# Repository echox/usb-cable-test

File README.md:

# USB Cable Tester
This is a simple tester for USB cables with USB A and Micro USB B.

## Usage

### Cable test
Connect a cable to both ends of the tester. All four LEDs should light up.

If a LED isn't lighting up the corresponding wire might be broken or not connected.
Some cables come without the wires for data transmitting. These type of cables is only suiteable for slow charging a device and can be easily detected if the LEDs for D+ and D- are not connected.

### Battery test
To check if the battery is working disconnect any connected cable.
Press the button. All LEDs should light up.

### Testpads
You can also use the testpads for checking the data lines of your cable.
Connect a probe of your multimeter to TP1 and then check every other testpad for a connection.

## Build
The build is straightforward but contains SMD components with a small footprint (0603).
See the [bom.md](bom.md) for details.

The board and schematics were created with [https://kicad-pcb.org/](KiCad) and can be found in the `board/` directory.

I used OSHPark for manufactoring, you can order this version directly at //TODO add OSHPark link 

Have fun.

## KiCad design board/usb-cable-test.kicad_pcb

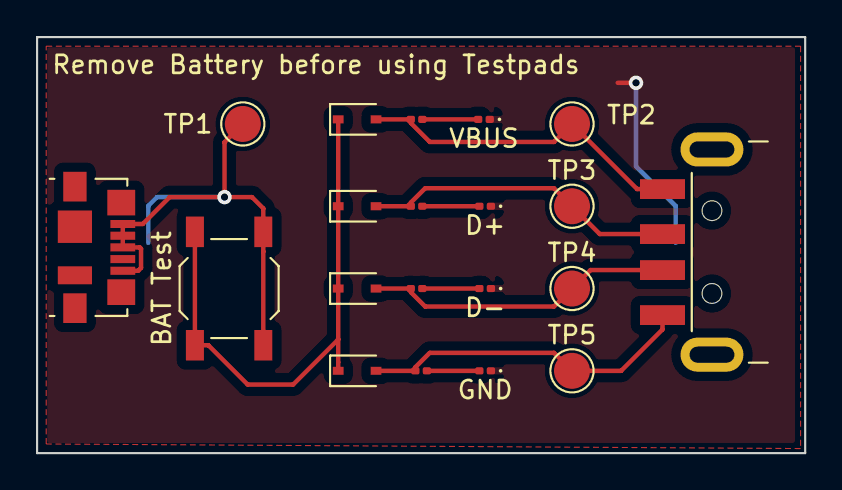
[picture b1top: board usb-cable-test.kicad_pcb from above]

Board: 2 copper layers, 42.7 x 23.1 mm, 21 parts (1 on the bottom side), 11 nets.

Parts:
CR2032: Battery_Cell; BatteryHolder_Keystone_1060_1x2032
D1, D2, D3, D4: 1n4148; D_SOD-323
D+: LED; D_0201_0603Metric
D-: LED; D_0201_0603Metric
GND: LED; D_0201_0603Metric
J1: USB_A; USB_A_CNCTech_1001-011-01101_Horizontal
J2: USB_B_Micro; USB_Micro-B_Molex_47346-0001
R1, R2, R3, R4: 5,1; R_0201_0603Metric
SW1: BAT Test; SW_SPST_TL3342
TP1, TP2, TP3, TP4, TP5: TestPoint; TestPoint_Pad_D2.0mm
VBUS: LED; D_0201_0603Metric

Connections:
unnamed: CR2032.1, J2.1, J2.2, J2.3, J2.5, SW1.1, TP1.1
unnamed: CR2032.2, D+.1, D-.1, GND.1, VBUS.1
unnamed: D1.1, D2.1, D3.1, D4.1, SW1.2
unnamed: D1.2, J1.1, R1.2, TP2.1
unnamed: D2.2, J1.2, R2.2, TP3.1
unnamed: D3.2, J1.3, R3.2, TP4.1
unnamed: D4.2, J1.4, R4.2, TP5.1
unnamed: R1.1, VBUS.2
unnamed: D+.2, R2.1
unnamed: D-.2, R3.1
unnamed: GND.2, R4.1

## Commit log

2020-02-26 added ignore file
2020-02-26 init kicad files
2020-02-26 added bom
2020-02-26 bom table fix
2020-02-26 added readme content
2020-02-26 formatting
